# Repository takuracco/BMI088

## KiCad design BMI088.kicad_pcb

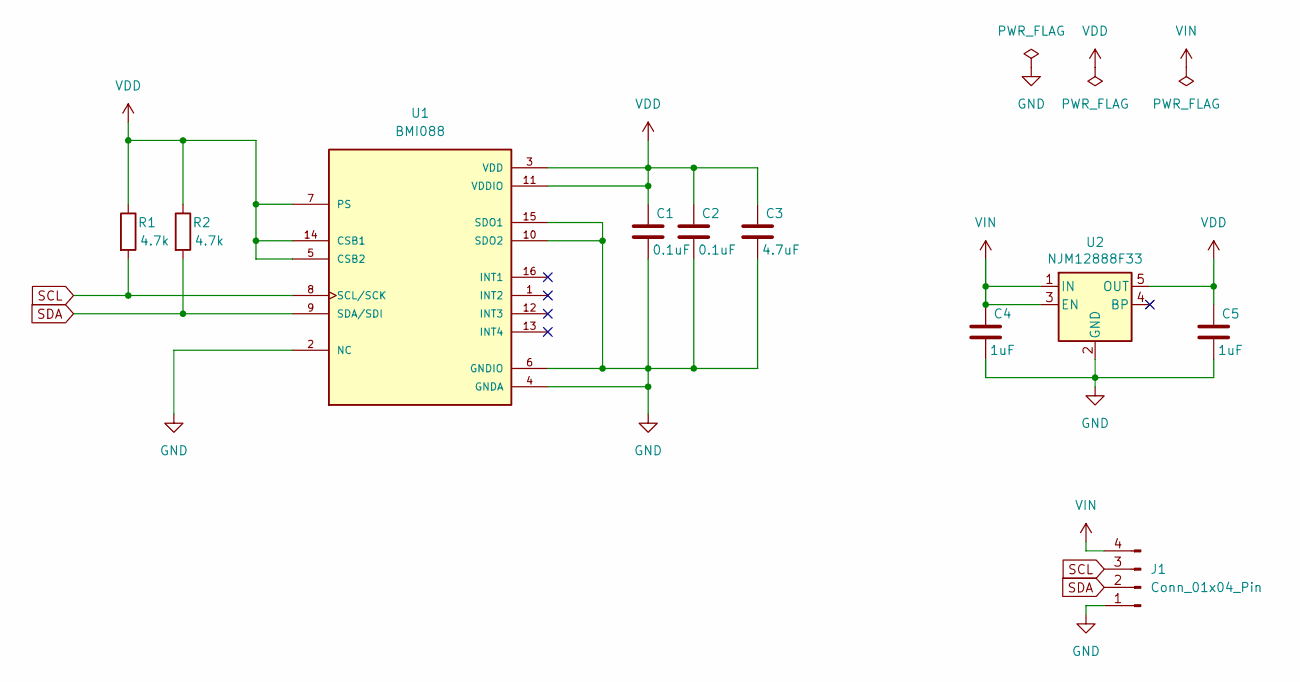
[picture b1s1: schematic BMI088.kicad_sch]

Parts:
C1, C2: 0.1uF; C_0603_1608Metric
C3: 4.7uF; C_0603_1608Metric
C4, C5: 1uF; C_0603_1608Metric
J1: Conn_01x04_Pin; PinHeader_1x04_P2.54mm_Vertical
R1, R2: 4.7k; R_0603_1608Metric
U1: BMI088; PQFN50P450X300X100-16N
U2: NJM12888F33; SOT-23-5; LCSC C37970

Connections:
GND: C1.2, C2.2, C3.2, C4.2, C5.2, J1.1, U1.2 (NC), U1.4 (GNDA), U1.6 (GNDIO), U1.10 (SDO2), U1.15 (SDO1), U2.2 (GND)
SCL: J1.3, R1.2, U1.8 (SCL/SCK)
SDA: J1.2, R2.2, U1.9 (SDA/SDI)
VDD: C1.1, C2.1, C3.1, C5.1, R1.1, R2.1, U1.3 (VDD), U1.5 (CSB2), U1.7 (PS), U1.11 (VDDIO), U1.14 (CSB1), U2.5 (OUT)
VIN: C4.1, J1.4, U2.1 (IN), U2.3 (EN)

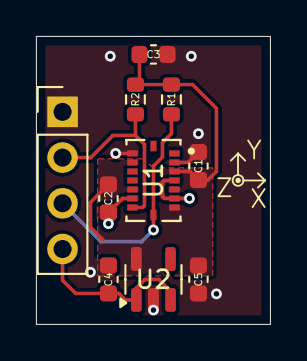
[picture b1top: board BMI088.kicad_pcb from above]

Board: 2 copper layers, 13.0 x 16.0 mm, 10 parts (0 on the bottom side), 5 nets.

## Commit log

2026-01-04 make readme
